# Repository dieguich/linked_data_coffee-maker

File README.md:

linked_data_coffee-maker
========================

This is a project related to the design of a coffee maker which is able to sense its energy data and to store the breakdown of it in a remote Database as RDF triples.

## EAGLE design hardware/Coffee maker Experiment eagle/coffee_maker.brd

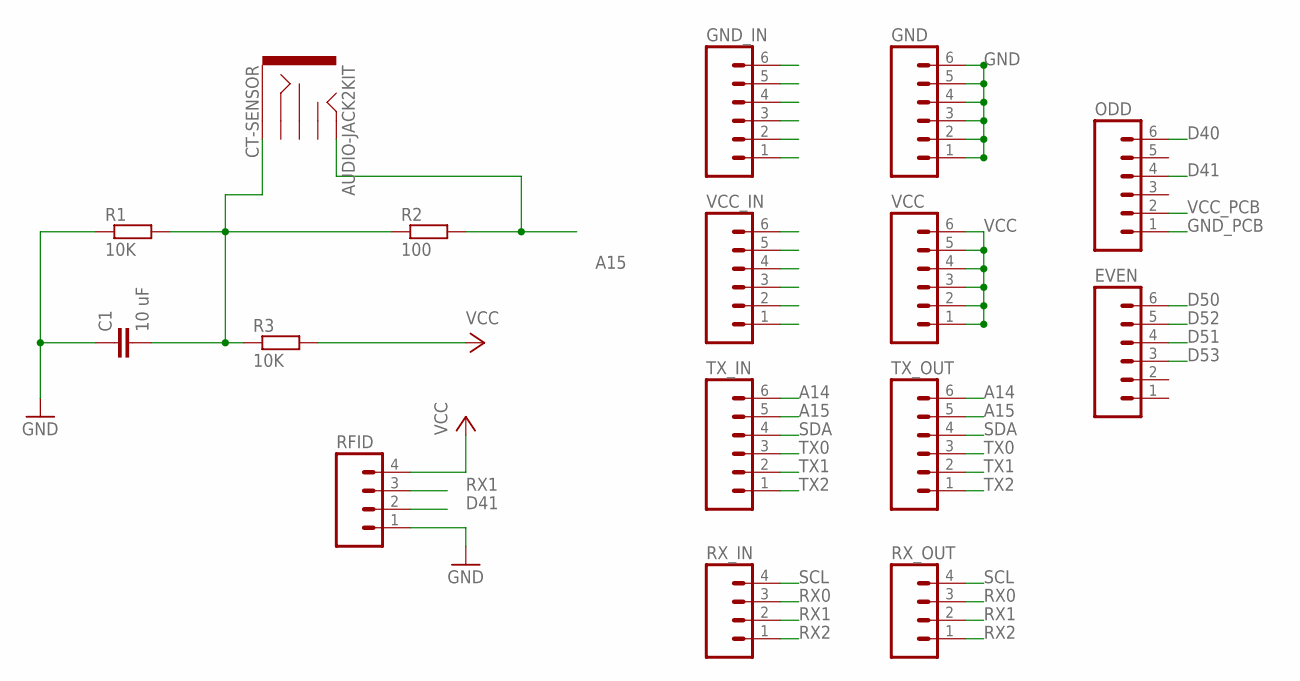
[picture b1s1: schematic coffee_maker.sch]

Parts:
C1: 10 uF; C1206
CT-SENSOR: AUDIO-JACK2KIT; AUDIO-JACK-KIT
EVEN: M06SIP; 1X06
GND: M06SIP; 1X06
GND_IN: M06SIP; 1X06
ODD: M06SIP; 1X06
R1, R3: 10K; M1206
R2: 100; M1206
RFID: M04SMD2; 1X04-1MM-RA
RX_IN: M04PTH; 1X04
RX_OUT: M04PTH; 1X04
TX_IN: M06SIP; 1X06
TX_OUT: M06SIP; 1X06
VCC: M06SIP; 1X06
VCC_IN: M06SIP; 1X06

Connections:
A14: TX_IN.6, TX_OUT.6
A15: CT-SENSOR.TIP, R2.2, TX_IN.5, TX_OUT.5
D40: ODD.6
D41: ODD.4, RFID.2
D50: EVEN.6
D51: EVEN.4
D52: EVEN.5
D53: EVEN.3
GND: C1.1, GND.1, GND.2, GND.3, GND.4, GND.5, GND.6, GND_IN.6, R1.1, RFID.1
GND_PCB: ODD.1
unnamed: C1.2, CT-SENSOR.SLEEVE, R1.2, R2.1, R3.1
RX0: RX_IN.3, RX_OUT.3
RX1: RFID.3, RX_IN.2, RX_OUT.2
RX2: RX_IN.1, RX_OUT.1
SCL: RX_IN.4, RX_OUT.4
SDA: TX_IN.4, TX_OUT.4
TX0: TX_IN.3, TX_OUT.3
TX1: TX_IN.2, TX_OUT.2
TX2: TX_IN.1, TX_OUT.1
VCC: R3.2, RFID.4, VCC.1, VCC.2, VCC.3, VCC.4, VCC.5, VCC.6, VCC_IN.1
VCC_PCB: ODD.2

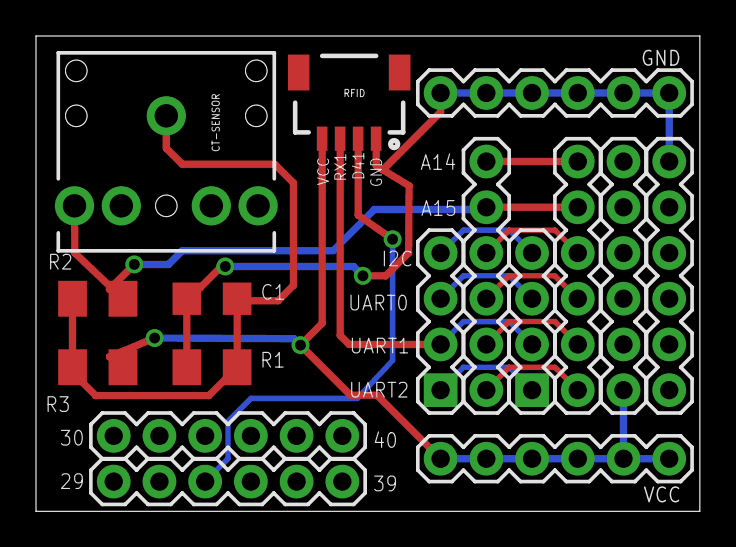
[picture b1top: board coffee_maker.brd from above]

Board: 2 copper layers, 36.9 x 26.4 mm, 16 parts (0 on the bottom side), 14 nets.

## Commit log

2013-11-11 first commit demo code
2013-11-11 README file modified
2013-11-11 upload dependencies, restclient
2013-11-11 first folder renames as -demo-
2013-11-11 remove all old
2013-12-11 const added to PROGMEM vars
2013-12-16 Change location of DDBB variables out of the function controlCoffeeMade()
2013-12-16 RFID output deleted
2014-01-21 major changes. Iboard used. All the code integrated with SD card confing file
2014-01-24 RTC integrated in code. Now the Time is gotten from Iboard-RTC
2014-01-24 RFID issues solved. POST working. status = mature.
2014-01-27 struct IPs definition changed
2014-01-27 code refactoring. RTC.getTime() in each print function. time_secs --> time
2014-01-27 dependecies list updated in README.md
2014-01-27 directory renamed
2014-01-27 LEDs code updated. Only one light pin D13. Now for debuggin whenever fails, the TEST LEDS will turn into red steadily. Failure detected and solved in IniFile.
2014-03-24 Watchdog added to restart the Arduino everyday. This is to avoid problems with the IP expiration
2014-06-03 RTC issue updated and delay subtracted from variable timeOn
2014-06-03 change name: from computing_techabout to nespresso
2014-06-03 update computing to nespresso
2014-06-03 file renamed
2014-08-13 File for forecast and Arduino added
2014-08-13 add readme
2014-08-14 add server code
2014-08-14 new readme
2014-08-14 changes I do not remember but they are important
2014-08-14 changes I do not remember but they are important 2
2015-02-26 Secure the Ethernet restart in Wikitoki, MORElab and Bailen. Change the date to not add anymore one hour to the data fetched. Add headers with modifications
2015-02-26 euskaltegi modified. Stray errors corrected
2016-05-19 Eagle of the board for connecting the current sensor and the RFID reader

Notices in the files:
parts and their libraries:
SparkFun-Connectors: Licensing: CC v3.0 Share-Alike You are welcome to use this library for commercial purposes.
